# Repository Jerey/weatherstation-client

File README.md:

# Weatherstation - Client

## Idea

The idea was to create a platform tracking various climate data, which can be extended and has no dependencies to the visualization. Therefore a network based solution was chosen.
<sup>[1](#EnergyConsumption)</sup>

As basis for the project a D1-mini was chosen, as it comes with onboard WiFi. But also other platforms can be used (e.g.: NodeMCU, ...).

The idea is to read the sensor data and send it via MQTT. Anyone who wants to use the data, can simply subscribe to the topic `/esp/#`. To indicate the type of data, the messages are defined by a MAC (to know from which client the message comes from), the type of data and the value. In this case, the topic holds this information in following structure: `/esp/MAC_ADDRESS/TYPE_OF_DATA/`

Have a look at [Weatherstation Server](https://github.com/jerey/weatherstation-server).

## Current State

Currently, two parameters are published:

1. Temperature
2. Humidity

Further can be added by using a different or further sensor.

## Visualization of Data

How the data is visualized is pretty much up to the user. Either one can use another D1-mini with an attached display, or one can use a server, which collects the data and visualizes it in a browser.

## Setup

The setup is split up into two areas: hardware setup and software setup.

### Hardware

The list of needed hardware is as follows:

- D1 Mini or an ESP 01
- BME 280
- 2 x 4k7 Ohm Resistor
- Button

#### D1 Mini setup

Following is the schematic for this setup with an **D1 Mini**.

Note: The BME280 was added with wires to get a more precise temperature. Initially it was also added to the base shield, but there the temperature was always a bit higher.

#### ESP 01 setup

If you want to reduce power consumption even more, you can use the **ESP01**.

Following pins from the [D1 mini](#d1-mini-setup) have to be changed then:

- `D3` :arrow_right: `Pin 0`
- `D4` :arrow_right: `Pin 2`

Further, to enable deep sleep, a little soldering has to be done. There are several tutorials in the internet for that, so I will not go into that here.

### Software

As basis for the software, platform IO was used as it comes with a good library management and makes flashing rather easy. But first have a look into the code.

#### Software settings

The software allows several settings within the `program.cpp`. There are more than the mentioned ones, but those are the most important ones:

1. `BME280_I2C_ADDR` - Depending on the used BME280, there are different I^2^C addresses in use. The used library offers a way to set this address, as described [here](https://github.com/adafruit/Adafruit_BME280_Library/issues/15). Usually the address is either `0x76` or `0x77`. Please check the datasheet of the used BME280 and set the value.
2. `ssidAP` & `passwordAP` - The SSID and password of the accesspoint, which the hardware starts, in case it cannot connect to any wifi. One can then look for the wifi `ssidAP` and connect to it with the password `passwordAP`.
3. `updateFrequency` - The frequency of updates of the parameters/values to be sent to the network. Defined in milliseconds.

#### Flashing

Install platformIO as described on their [webpage](https://docs.platformio.org/en/latest/core.html).
If you chose platformIO for the CLI, you can execute following command from the terminal: `platformio run --target upload`
If you use an ide, please refer to the [platformIO documenation](https://docs.platformio.org/en/latest/ide/pioide.html).

## Documentation

This chapter aims to describe some essential parts of the software.

## Usage of the client

When the software is flashed, the client will directly start. If it has not been configured previously, it will open up an accesspoint. Otherwise it will simply reconnect to the last configured WiFi and start publishing the data.

### Accesspoint at the beginning

When the client is started, the [WiFiManager](https://github.com/tzapu/WiFiManager) is being used to check, whether it has any known WiFi available to connect to. If it either does not know any WiFi or cannot connect to one, it opens up an access point and provides an user interface to setup the desired WiFi. From that point on, it will always try to connect to that WiFi. If you want to connect to another WiFi, press the button added to the board and the access point will again be opened.

### Flashing software to several clients

Work in progress: It currently is possible to flash several clients at once. The [ESP8266httpUpdate](https://github.com/esp8266/Arduino/tree/master/libraries/ESP8266httpUpdate) library is used to auto update the firmware, if the defined update server provides any new firmware. This decision is based on a version defined in the `program.cpp`. For now a python flask server is used as update server. This is currently based on the docker image [esp-update-server](https://hub.docker.com/r/kstobbe/esp-update-server/). For more information on that, checkout the [readme.md](https://github.com/kstobbe/esp-update-server).

## Some Images

On a breadboard:

Further, one can also buy base shields and then solder all parts together:

## Footnotes

<a name="EnergyConsumption">1</a>: For the purpose of the project, the network based solution is fine, but if one wants to tweak the energy consumption to a minimum, other options should be considered (e.g.: Bluetooth Low Energy (BLE), ...).

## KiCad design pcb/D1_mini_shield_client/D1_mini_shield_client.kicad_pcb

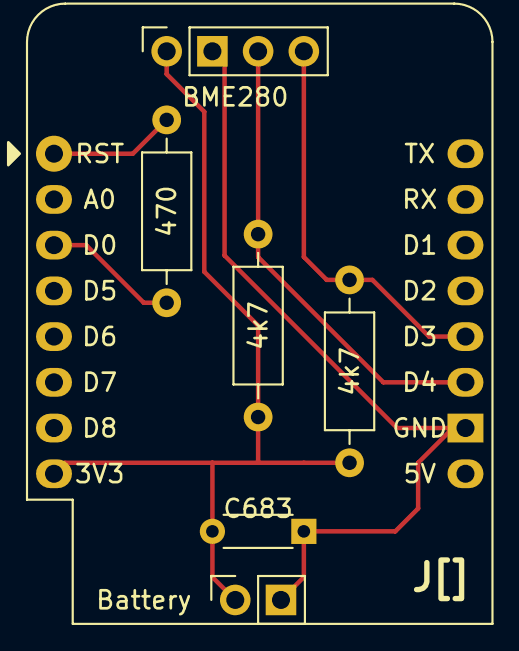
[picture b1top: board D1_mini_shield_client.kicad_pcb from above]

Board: 2 copper layers, 7 parts (0 on the bottom side), 6 nets.

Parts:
C683: C; R_Axial_DIN0204_L3.6mm_D1.6mm_P5.08mm_Horizontal
J1: BME280; PinSocket_1x04_P2.54mm_Vertical
J2: Battery; PinSocket_1x02_P2.54mm_Vertical
R1, R3: 4k7; R_Axial_DIN0207_L6.3mm_D2.5mm_P10.16mm_Horizontal
R2: 470; R_Axial_DIN0207_L6.3mm_D2.5mm_P10.16mm_Horizontal
U1: WeMos_mini; WEMOS_D1_mini_light_correctpins

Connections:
/3V3: C683.2, J1.1, J2.1, R1.1, R3.1, U1.16
/D0: R2.1, U1.11
/D3: J1.4, R1.2, U1.4
/D4: J1.3, R3.2, U1.3
/GND: C683.1, J1.2, J2.2, U1.2
/RST: R2.2, U1.9

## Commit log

2019-02-08 Weatherstation Client to broadcast climate data.
    Please see the readme for further information.
2019-04-26 Adds the link to a compatible server.
2019-06-21 Make use of PlatformIO and testing.
2019-06-21 Add target.
2019-06-21 Add initial travis configuration.
2019-06-21 Add c++ version.
2019-06-21 Add build status from travis.
2019-06-21 Replace handdrawn schematic.
2019-06-22 Improve unit tests.
2019-06-22 Improve tests with even more constness.
2019-06-22 Explicit constructors.
2019-08-12 Add update server for the firmware.
2019-08-12 Update readme with references to auto update.
2019-10-01 Add missing resistor for the schematic.
2019-10-03 Introduce MQTT to the client.
    Todo:
    - Adapt the documentation.
    - Adapt the server.
2019-10-03 Remove the messages
    The messages are now no longer needed. This is handled via MQTT now.
    Therefore the messages are deleted, their tests are no longer required and since the program.cpp currently is not tested, travis is for now also remove.
2019-10-03 Adapt the readme.
2019-10-05 Remove unnecessary slashes.
2019-11-09 DeepSleep and remove wifi config button
    - Deep sleep has now been activated.
    - The wifi configuration button has been removed.
2019-12-30 Disconnect after publishing new sensor data.
    Reconnection errors to the MQTT broker can occur if the client simply disconnects due to deep sleep.
    Therefore disconnecting from the broker properly is essential.
2020-01-02 Measure the current voltage and publish.
2020-01-11 Apply clang-format on code.
2020-01-11 Use unsigned for unsigned counter.
2020-03-08 Add a common function for publishing values.
2020-03-08 Remove wrong line.
2020-04-24 Update readme.
2020-08-27 Update username.
2020-10-14 Add clang-format and code cleanup.
2020-10-14 Fix readme.
2021-01-06 Add first pcb prototype.
2022-10-01 Update pcb.
2023-01-29 Remove update server for now.
2023-01-29 Add Github Actions build.
2023-01-29 Modernize defines.
2023-02-13 Remove the table of contents since github provides it.
2023-07-01 Add config portal timeout.
2023-07-01 Update BME library.
